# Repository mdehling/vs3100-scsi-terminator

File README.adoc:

= VAXstation 3100 SCSI Terminator
Malte Dehling <mdehling@gmail.com>

:imagesdir: https://raw.githubusercontent.com/mdehling/vs3100-scsi-terminator/main/img/

:url-vs3100-scsi: https://www.xanthos.se/~joachim/DEC_SCSI.html
:url-TE-Connectivity: https://www.te.com/

This is a replacement for the VAXstation 3100 SCSI Terminator.  The 68-pin
connector is SCSI-1 SE with a {url-vs3100-scsi}[proprietary pinout], _not_
wide SCSI!  Your only options are to buy an original SCSI Terminator (DEC P/N
12-29635-01) or to make your own.

Parts
-----
These are the parts I use:

[%autowidth]
|===
| Designator | Quantity | Description

| J1         | 1        | T/E 786555-7
| RN1, RN2   | 2        | Bourns 4611X-104-221/331
|===

I would like to thank the folks at {url-TE-Connectivity}[T/E Connectivity] for
sending me free samples of their connectors.

Assembly
--------
Just solder on the parts, but make sure to get their orientation right!  Check
these images to see what the result should look like:

link:{imagesdir}front.jpg[image:front.jpg["Front Side",width=32%]]
link:{imagesdir}back.jpg[image:back.jpg["Back Side",width=32%]]
link:{imagesdir}angle.jpg[image:angle.jpg["At an Angle",width=32%]]

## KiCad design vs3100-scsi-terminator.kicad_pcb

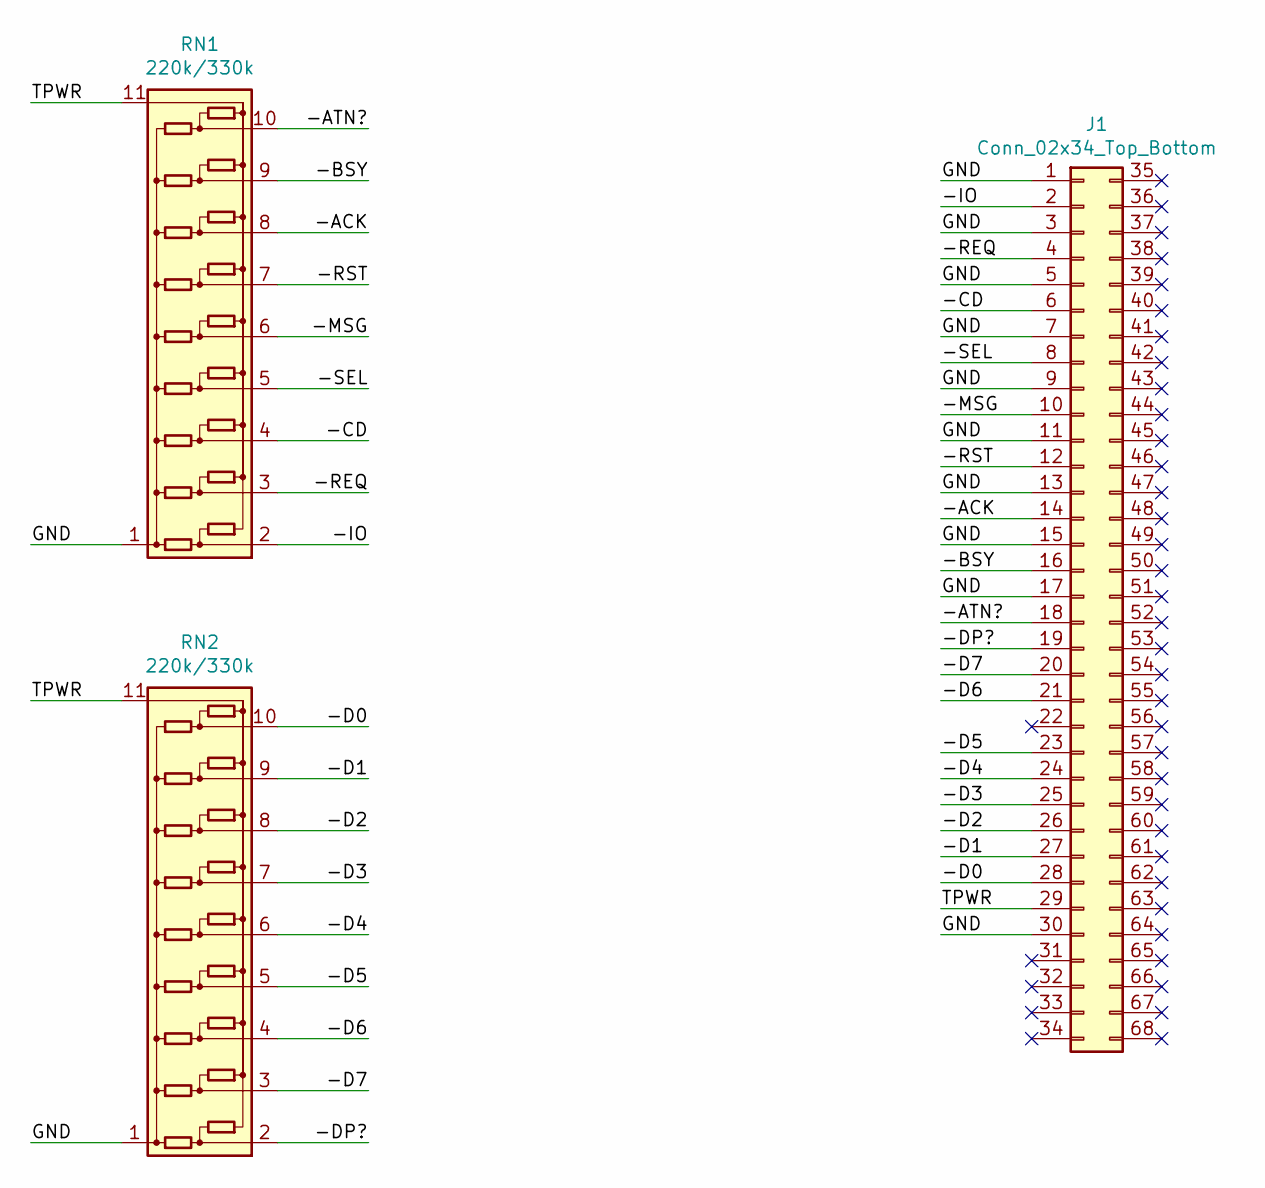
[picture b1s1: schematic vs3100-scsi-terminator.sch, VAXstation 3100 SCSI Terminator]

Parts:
J1: Conn_02x34_Top_Bottom; TE_786555-7
RN1, RN2: 220k/330k; R_Array_SIP11

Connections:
/-ACK: J1.14, RN1.8 (R7)
/-ATN?: J1.18, RN1.10 (R9)
/-BSY: J1.16, RN1.9 (R8)
/-CD: J1.6, RN1.4 (R3)
/-D0: J1.28, RN2.10 (R9)
/-D1: J1.27, RN2.9 (R8)
/-D2: J1.26, RN2.8 (R7)
/-D3: J1.25, RN2.7 (R6)
/-D4: J1.24, RN2.6 (R5)
/-D5: J1.23, RN2.5 (R4)
/-D6: J1.21, RN2.4 (R3)
/-D7: J1.20, RN2.3 (R2)
/-DP?: J1.19, RN2.2 (R1)
/-IO: J1.2, RN1.2 (R1)
/-MSG: J1.10, RN1.6 (R5)
/-REQ: J1.4, RN1.3 (R2)
/-RST: J1.12, RN1.7 (R6)
/-SEL: J1.8, RN1.5 (R4)
/GND: J1.1, J1.3, J1.5, J1.7, J1.9, J1.11, J1.13, J1.15, J1.17, J1.30, RN1.1 (COM1), RN2.1 (COM1)
/TPWR: J1.29, RN1.11 (COM2), RN2.11 (COM2)

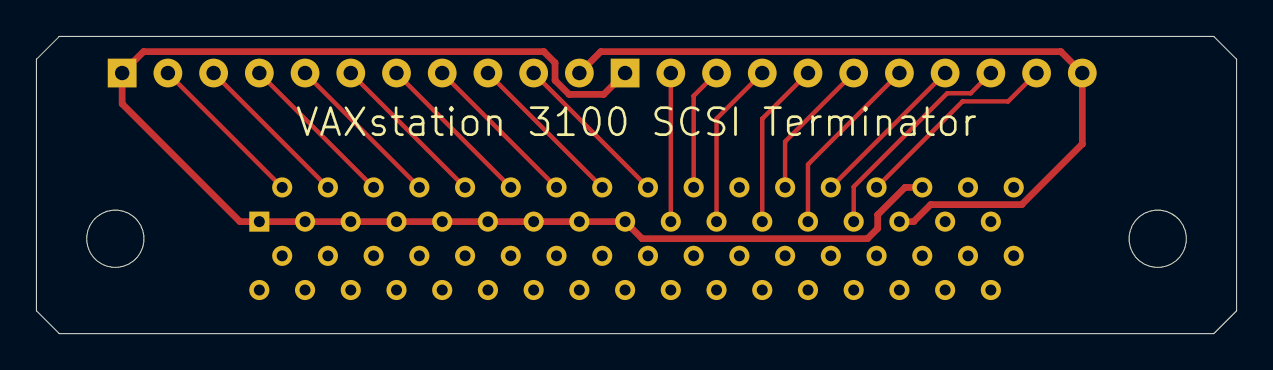
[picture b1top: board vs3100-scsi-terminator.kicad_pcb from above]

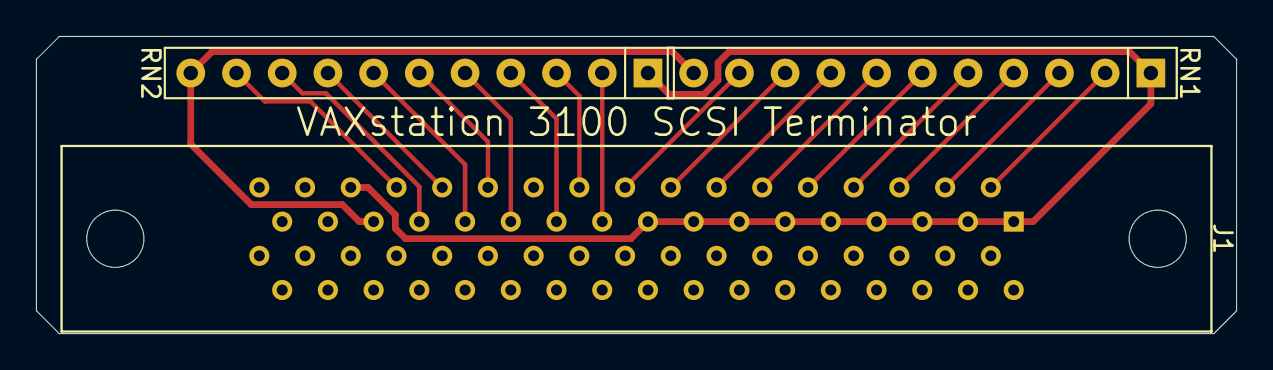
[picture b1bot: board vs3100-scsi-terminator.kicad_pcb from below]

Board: 2 copper layers, 66.7 x 16.5 mm, 3 parts (3 on the bottom side), 20 nets.

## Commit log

2021-05-06 Add photos
2021-05-06 Add pinout link
2022-05-27 Update image URLs
